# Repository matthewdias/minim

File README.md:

# minim
A symmetrical 50% keyboard

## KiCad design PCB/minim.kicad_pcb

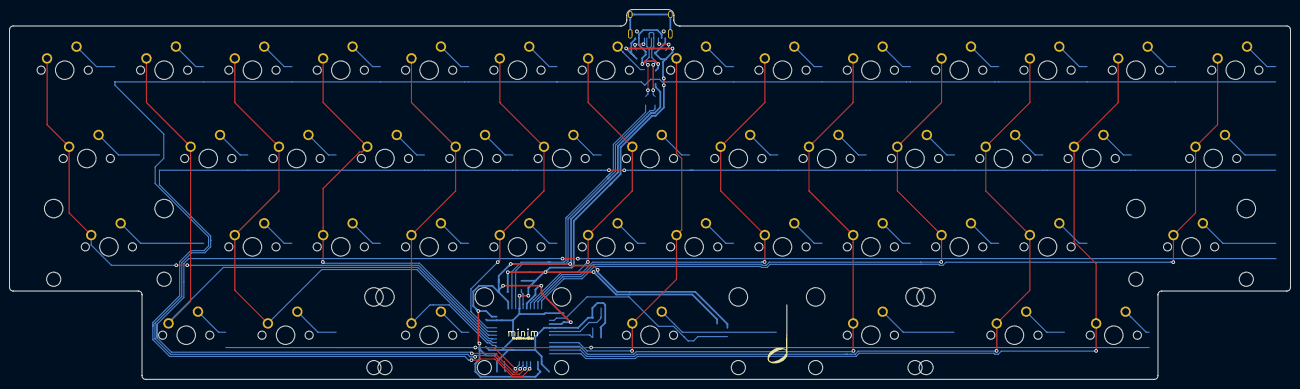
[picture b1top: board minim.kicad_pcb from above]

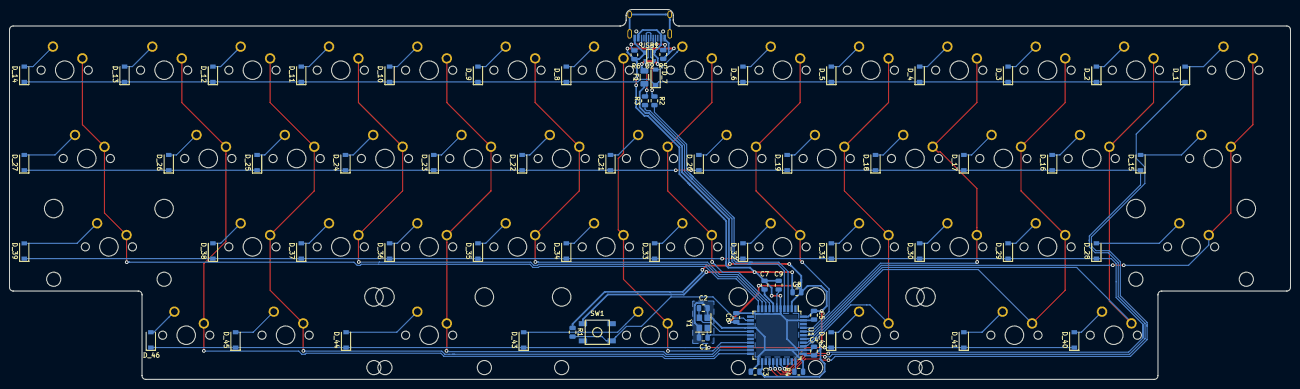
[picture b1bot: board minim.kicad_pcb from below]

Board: 2 copper layers, 276.2 x 79.8 mm, 114 parts (67 on the bottom side), 78 nets.

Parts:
C1, C2: 22pF; C_0805_2012Metric
C3, C4, C5, C6, C7: 0.1uF; C_0805_2012Metric
C8: 10uF; C_0805_2012Metric
C9: 1uF; C_0805_2012Metric
D_1, D_2, D_3, D_4, D_5, D_6, D_7, D_8, D_9, D_10, D_11, D_12, D_13, D_14, D_15, D_16, D_17, D_18, D_19, D_20, D_21, D_22, D_23, D_24, D_25, D_26, D_27, D_28, D_29, D_30, D_31, D_32, D_33, D_34, D_35, D_36, D_37, D_38, D_39, D_40, D_41, D_42, D_43, D_44, D_45, D_46: D; D_SOD-123
F1: 500mA; Fuse_1206_3216Metric
K_1, K_14, K_41, K_45: KEYSW; MXOnly-1.25U-NoLED
K_2, K_3, K_4, K_5, K_6, K_7, K_8, K_9, K_10, K_11, K_12, K_13, K_16, K_17, K_18, K_19, K_20, K_21, K_22, K_23, K_24, K_25, K_26, K_29, K_30, K_31, K_32, K_33, K_34, K_35, K_36, K_37, K_38, K_40, K_46: KEYSW; MXOnly-1U-NoLED
K_15, K_27: KEYSW; MXOnly-1.75U-NoLED
K_28, K_39: KEYSW; MXOnly-2.25U-ReversedStabilizers-NoLED
K_42, K_44: KEYSW; MXOnly-2U-ReversedStabilizers-NoLED
K_43: KEYSW; MXOnly-7U-3U-ReversedStabilizers-NoLED - Copy
LOGO1: LOGO; icon
R1, R4: 10k; R_0805_2012Metric
R2, R3: 22; R_0805_2012Metric
R5, R6: 5.1k; R_0805_2012Metric
SW1: SW_Push; SKQG-1155865
U1: ATmega32U4-AU; TQFP-44_10x10mm_P0.8mm
U2: PRTR5V0U2X; SOT143B
USB1: HRO-TYPE-C-31-M-12; HRO-TYPE-C-31-M-12-Assembly
Y1: 16MHz; Crystal_SMD_3225-4Pin_3.2x2.5mm

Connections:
+5V: C3.1, C4.1, C5.1, C6.1, C7.1, C8.1, F1.1, R1.1, U1.2, U1.7, U1.14, U1.24, U1.34, U1.44
D+: R3.1, U1.4
D-: R2.1, U1.3
GND: C1.2, C2.2, C3.2, C4.2, C5.2, C6.2, C7.2, C8.2, C9.2, R4.1, R5.1, R6.1, SW1.1, U1.5, U1.15, U1.23, U1.35, U1.43, U2.1, USB1.1, USB1.12, Y1.2, Y1.4
unnamed: C1.1, U1.17, Y1.1
unnamed: C2.1, U1.16, Y1.3
unnamed: C9.1, U1.6
unnamed: D_1.2, K_1.2
unnamed: D_2.2, K_2.2
unnamed: D_3.2, K_3.2
unnamed: D_4.2, K_4.2
unnamed: D_5.2, K_5.2
unnamed: D_6.2, K_6.2
unnamed: D_7.2, K_7.2
unnamed: D_8.2, K_8.2
unnamed: D_9.2, K_9.2
unnamed: D_10.2, K_10.2
unnamed: D_11.2, K_11.2
unnamed: D_12.2, K_12.2
unnamed: D_13.2, K_13.2
unnamed: D_14.2, K_14.2
unnamed: D_15.2, K_15.2
unnamed: D_16.2, K_16.2
unnamed: D_17.2, K_17.2
unnamed: D_18.2, K_18.2
unnamed: D_19.2, K_19.2
unnamed: D_20.2, K_20.2
unnamed: D_21.2, K_21.2
unnamed: D_22.2, K_22.2
unnamed: D_23.2, K_23.2
unnamed: D_24.2, K_24.2
unnamed: D_25.2, K_25.2
unnamed: D_26.2, K_26.2
unnamed: D_27.2, K_27.2
unnamed: D_28.2, K_28.2
unnamed: D_29.2, K_29.2
unnamed: D_30.2, K_30.2
unnamed: D_31.2, K_31.2
unnamed: D_32.2, K_32.2
unnamed: D_33.2, K_33.2
unnamed: D_34.2, K_34.2
unnamed: D_35.2, K_35.2
unnamed: D_36.2, K_36.2
unnamed: D_37.2, K_37.2
unnamed: D_38.2, K_38.2
unnamed: D_39.2, K_39.2
unnamed: D_40.2, K_40.2
unnamed: D_41.2, K_41.2
unnamed: D_42.2, K_42.2
unnamed: D_43.2, K_43.2
unnamed: D_44.2, K_44.2
unnamed: D_45.2, K_45.2
unnamed: D_46.2, K_46.2
unnamed: R1.2, SW1.2, U1.13
unnamed: R2.2, U2.3, USB1.5, USB1.7
unnamed: R3.2, U2.2, USB1.6, USB1.8
unnamed: R4.2, U1.33
unnamed: R5.2, USB1.4
unnamed: R6.2, USB1.10
VCC: F1.2, U2.4, USB1.2, USB1.11
col0: K_1.1, K_15.1, K_28.1, U1.39
col1: K_2.1, K_16.1, K_40.1, U1.38
col2: K_3.1, K_17.1, K_29.1, K_41.1, U1.37
col3: K_4.1, K_18.1, K_30.1, U1.40
col4: K_5.1, K_19.1, K_31.1, K_42.1, U1.36
col5: K_6.1, K_20.1, K_32.1, U1.41
col6: K_7.1, K_21.1, K_33.1, U1.8
col7: K_8.1, K_34.1, K_43.1, U1.19
col8: K_9.1, K_22.1, K_35.1, U1.9
col9: K_10.1, K_23.1, K_36.1, K_44.1, U1.20
col10: K_11.1, K_24.1, K_37.1, U1.10
col11: K_12.1, K_25.1, K_38.1, K_45.1, U1.21
col12: K_13.1, K_26.1, K_46.1, U1.22
col13: K_14.1, K_27.1, K_39.1, U1.11
row0: D_1.1, D_2.1, D_3.1, D_4.1, D_5.1, D_6.1, D_7.1, D_8.1, D_9.1, D_10.1, D_11.1, D_12.1, D_13.1, D_14.1, U1.26
row1: D_15.1, D_16.1, D_17.1, D_18.1, D_19.1, D_20.1, D_21.1, D_22.1, D_23.1, D_24.1, D_25.1, D_26.1, D_27.1, U1.27
row2: D_28.1, D_29.1, D_30.1, D_31.1, D_32.1, D_33.1, D_34.1, D_35.1, D_36.1, D_37.1, D_38.1, D_39.1, U1.28
row3: D_40.1, D_41.1, D_42.1, D_43.1, D_44.1, D_45.1, D_46.1, U1.29

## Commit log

2020-11-15 Add PCB files
2020-11-15 Add PCB Readme
2020-11-15 Add pics
2020-11-15 Add case files
2020-11-15 Add layout image
